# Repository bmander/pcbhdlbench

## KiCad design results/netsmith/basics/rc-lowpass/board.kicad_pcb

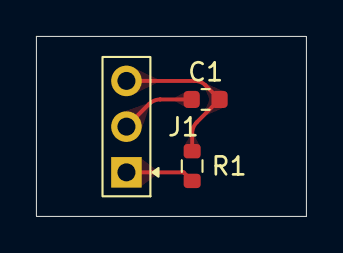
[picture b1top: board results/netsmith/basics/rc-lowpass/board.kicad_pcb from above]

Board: 2 copper layers, 15.0 x 10.0 mm, 3 parts (0 on the bottom side), 3 nets.

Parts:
C1: 100n; C_0603_1608Metric
J1: Header1x3; PinHeader_pins3_pitch2.54mm_rows1
R1: 10k; R_0603_1608Metric

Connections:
net-c1.a: C1.1, J1.3, R1.2
net-c1.b: C1.2, J1.2
net-j1.p1: J1.1, R1.1

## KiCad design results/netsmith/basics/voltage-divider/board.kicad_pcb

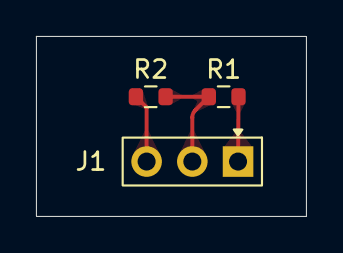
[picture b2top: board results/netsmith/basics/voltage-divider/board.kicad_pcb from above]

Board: 2 copper layers, 15.0 x 10.0 mm, 3 parts (0 on the bottom side), 3 nets.

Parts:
J1: Header1x3; PinHeader_pins3_pitch2.54mm_rows1
R1, R2: 10k; R_0603_1608Metric

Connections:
net-j1.p1: J1.1, R1.1
net-j1.p2: J1.2, R1.2, R2.1
net-j1.p3: J1.3, R2.2

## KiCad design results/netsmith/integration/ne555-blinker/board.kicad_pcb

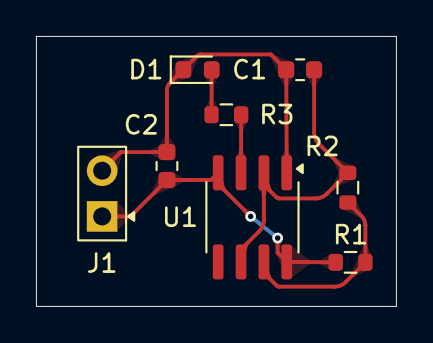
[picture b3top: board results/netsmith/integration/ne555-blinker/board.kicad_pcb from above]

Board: 2 copper layers, 20.0 x 15.0 mm, 8 parts (0 on the bottom side), 6 nets.

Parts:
C1: 1u; C_0603_1608Metric
C2: 100n; C_0603_1608Metric
D1: KT-0603R; LED_0603_1608Metric
J1: Conn_01x02; PinHeader_1x02_P2.54mm_Vertical
R1: 1k; R_0603_1608Metric
R2: 470k; R_0603_1608Metric
R3: 330; R_0603_1608Metric
U1: Soic8; SOIC-8_3.9x4.9mm_P1.27mm

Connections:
net-c1.a: C1.1, R2.2, U1.2, U1.6
net-c1.b: C1.2, C2.2, D1.1, J1.2, U1.1
net-c2.a: C2.1, J1.1, R1.1, U1.4, U1.8
net-d1.anode: D1.2, R3.2
net-r1.b: R1.2, R2.1, U1.7
net-r3.a: R3.1, U1.3

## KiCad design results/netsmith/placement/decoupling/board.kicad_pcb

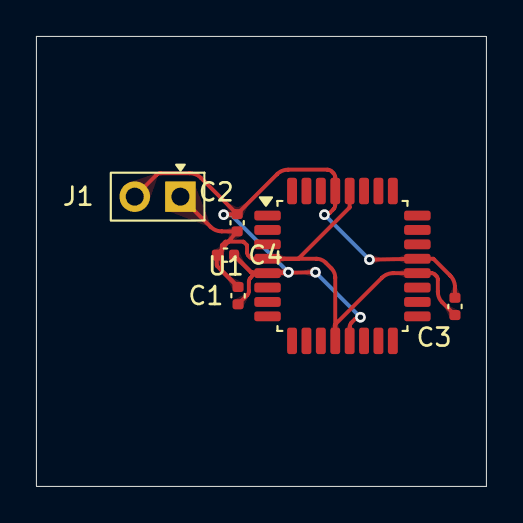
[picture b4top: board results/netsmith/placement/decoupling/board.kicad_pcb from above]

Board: 2 copper layers, 25.0 x 25.0 mm, 6 parts (0 on the bottom side), 2 nets.

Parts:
C1, C2, C3, C4: 100n; C_0402_1005Metric
J1: Conn_01x02; PinHeader_1x02_P2.54mm_Vertical
U1: Tqfp32; TQFP-32_7x7mm_P0.8mm

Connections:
net-c1.a: C1.1, C2.1, C3.1, C4.1, J1.1, U1.4, U1.12, U1.20, U1.28
net-c1.b: C1.2, C2.2, C3.2, C4.2, J1.2, U1.5, U1.13, U1.21, U1.29

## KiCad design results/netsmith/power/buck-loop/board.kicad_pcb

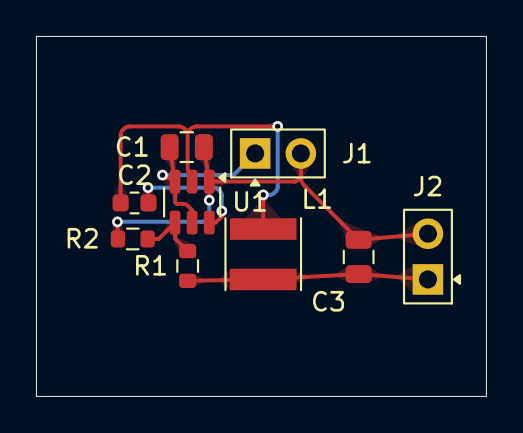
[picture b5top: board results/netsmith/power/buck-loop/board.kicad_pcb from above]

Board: 2 copper layers, 25.0 x 20.0 mm, 9 parts (0 on the bottom side), 6 nets.

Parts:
C1, C3: 47u; C_0805_2012Metric
C2: 100n; C_0603_1608Metric
J1, J2: Conn_01x02; PinHeader_1x02_P2.54mm_Vertical
L1: Inductor4x4; L_Taiyo-Yuden_NR-40xx
R1: 33k; R_0603_1608Metric
R2: 10k; R_0603_1608Metric
U1: Tps562201; SOT-23-6

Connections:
net-c1.a: C1.1, J1.1, U1.3, U1.5
net-c1.b: C1.2, C3.2, J1.2, J2.2, R2.2, U1.1
net-c2.a: C2.1, U1.6
net-c2.b: C2.2, L1.1, U1.2
net-c3.a: C3.1, J2.1, L1.2, R1.1
net-r1.b: R1.2, R2.1, U1.4

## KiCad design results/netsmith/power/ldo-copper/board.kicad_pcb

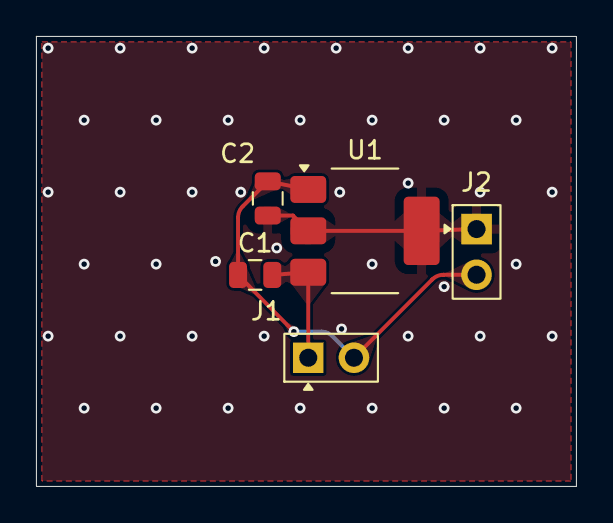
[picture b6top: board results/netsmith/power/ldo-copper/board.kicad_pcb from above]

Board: 2 copper layers, 30.0 x 25.0 mm, 5 parts (0 on the bottom side), 3 nets.

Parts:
C1, C2: 47u; C_0805_2012Metric
J1, J2: Conn_01x02; PinHeader_1x02_P2.54mm_Vertical
U1: Ldo1117; SOT-223-3_TabPin2

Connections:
VOUT: C2.1, J2.1, U1.2
net-c1.a: C1.1, J1.1, U1.3
net-c1.b: C1.2, C2.2, J1.2, J2.2, U1.1

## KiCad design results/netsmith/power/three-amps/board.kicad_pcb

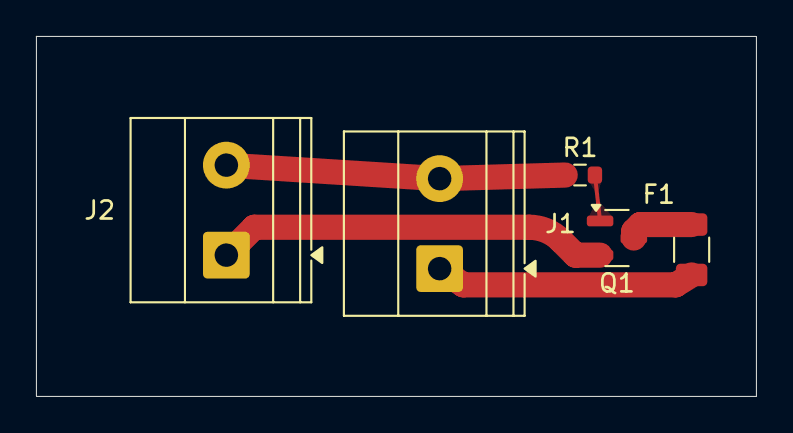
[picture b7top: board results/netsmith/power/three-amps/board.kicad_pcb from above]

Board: 2 copper layers, 40.0 x 20.0 mm, 5 parts (0 on the bottom side), 5 nets.

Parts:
F1: Fuse1206; Fuse_1206_3216Metric
J1, J2: Terminal2; TerminalBlock_Phoenix_MKDS-1,5-2_1x02_P5.00mm_Horizontal
Q1: PFetSot23; SOT-23
R1: 100k; R_0603_1608Metric

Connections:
net-f1.a: F1.1, J1.1
net-f1.b: F1.2, Q1.3
net-j1.p2: J1.2, J2.2, R1.2
net-j2.p1: J2.1, Q1.2
net-q1.gate: Q1.1, R1.1
